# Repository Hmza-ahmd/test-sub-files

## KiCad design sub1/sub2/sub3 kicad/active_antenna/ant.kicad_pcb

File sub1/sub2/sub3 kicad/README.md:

[updated 28 May 2018]

Click image for full size.

[© bluebison.net](http://bluebison.net)

KiwiSDR
=======

Software-defined Radio (SDR) and GPS for the BeagleBone Black
----------------------------------------------------------------------

An add-on board ("cape") that turns your Beagle into a web-accessible shortwave receiver.

This repository contains the KiCAD files (schematics, board layout), Gerbers, BOM and other files used to produce the KiwiSDR PCB.
Also included here is the design for an active antenna and bias tee.

**Note: the active antenna and bias tee schematics and PCBs here are still undergoing development and do not work properly. Do not fabricate the PCBs and expect them to work.**

The KiwiSDR software is located in the repository [Beagle_SDR_GPS](https://github.com/jks-prv/Beagle_SDR_GPS/).

### Kickstarter
KiwiSDR had a successful [Kickstarter](https://www.kickstarter.com/projects/1575992013/kiwisdr-beaglebone-software-defined-radio-sdr-with/).

### Details

* Listen live: [SDR.hu](https://sdr.hu/?top=kiwi), [kiwisdr.com](http://kiwisdr.com/public), [rx.linkfanel.net](http://rx.linkfanel.net)
* [Project webpage](http://www.kiwisdr.com/)
* [Operating information: installation, operation, FAQ](http://www.kiwisdr.com/quickstart/)
* Latest [source code commits](https://github.com/jks-prv/Beagle_SDR_GPS/commits/master)
* [Design review document](https://www.dropbox.com/s/i1bjyp1acghnc16/KiwiSDR.design.review.pdf?dl=1)
* [Schematic](http://www.kiwisdr.com/docs/KiwiSDR/kiwi.schematic.pdf), [Gerbers](http://www.kiwisdr.com/docs/KiwiSDR/kiwi.gerbers.tar), [Active antenna](http://www.kiwisdr.com/docs/KiwiSDR/ant.pdf), [BOM ODS](http://www.kiwisdr.com/docs/KiwiSDR/kiwi.bom.ods), [BOM XLS](http://www.kiwisdr.com/docs/KiwiSDR/kiwi.bom.xls)

### Description
This SDR is a bit different. It has a web interface that can be used by up to four separate listeners. Each one listening and tuning an independent frequency simultaneously. See the screenshots below.

### Components
* SDR covering the 10 kHz to 30 MHz (VLF-HF) spectrum.
* Web interface based on [OpenWebRX](http://openwebrx.org/) from András Retzler, HA7ILM.
* Integrated software-defined GPS receiver from Andrew Holme's [Homemade GPS Receiver](http://www.aholme.co.uk/GPS/Main.htm).
* LTC 14-bit 65 MHz ADC.
* Xilinx Artix-7 A35 FPGA.
* Skyworks SE4150L GPS front-end.

### Features
* 100% Open Source / Open Hardware.
* Browser-based interface allowing multiple simultaneous user web connections (currently 4).
* Each connection tunes an independent receiver channel over the entire spectrum.
* Waterfall tunes independently of audio and includes zooming and panning.
* Multi-channel, parallel DDC design using bit-width optimized CIC filters.
* Good performance at VLF/LF since we personally spend time monitoring those frequencies.
* Automatic frequency calibration via received GPS timing.
* Easy hardware and software setup. Browser-based configuration interface.

### Status

Give the live receivers a try at the links above. You'll need a recent version of a modern web browser that supports HTML5. The web interface works, with some problems, on mobile devices. But there is no mobile version of the interface yet.

The files of a KiCAD PCB layout of the cape are available. This PCB has been fabricated in production quantities
and shipped to thousands of customers worldwide.
Please email us any comments you have after reviewing the design document above. The active antenna and injector PCBs have been fabricated and are undergoing development.

### Objectives

We wanted to design an SDR that provides certain features, at a low price point, that we felt weren't covered by current devices. The SDR must be web-accessible and simple to setup and use.
We also wanted to provide a self-contained platform for experimentation with SDR and GPS techniques. 

Most importantly, We'd really like to see a significant number of web-enabled, wide-band SDRs deployed in diverse locations world-wide because that makes possible some really interesting applications and experiments.

### Operation

Users can purchase just the KiwiSDR board or a complete "kit" consisting of the board, BeagleBone Green (software pre-installed), enclosure (assembly required), and GPS antenna (see [here](http://www.kiwisdr.com/)).
The software will try to automatically open up an incoming port through whatever Internet firewall/router may exist on the local network, but the user may have to perform this step manually. An antenna solution must be provided. An adequate power supply to the Beagle (e.g. 5V @ 2A) will also be required.

Four channels of audio and waterfall streamed over the Internet 24/7 requires about 30 GB per month. This is a common cap for many residential broadband plans. An automatic dynamic-DNS system is already part of the software so a web link to the SDR is immediately available with no configuration. Of course the system can be configured to only allow connections from the local network and ignore Internet connection requests.

### Web interface screenshots

Click images for full size.

View of entire 0-30 MHz range:

Moderate zoom of medium-wave broadcast band with spectrum display on top enabled:

Over-the-horizon-radar (OTHR) from Cyprus showing short-term ionospheric fluctuations:

VLF/LF reception in New Zealand

| kHz | Station | Location | Signal |
| :-- | :------ | :------- | :----- |
| 12.88 | Alpha | Khabarovsk & Novosibirsk Russia | Navigation system |
| 17.0 | VTX2 | India | MSK comms |
| 19.8 | NWC | Australia | MSK comms |
| 21.4 | NPM | Hawaii | MSK comms |
| 22.2 | NDT/JJI | Japan | MSK comms |
| 24.1 | (UNID) | Korea, per David L Wilson | FSK comms |
| 40.0 | JJY | Japan | Time signal |
| 45.9 | NSY | Italy | MSK comms |
| 54.0 | NDI | Japan | MSK comms |
| 60.0 | JJY/WWVB | Japan, USA | Time signals |
| 68.5 | BPC | China | Time signal |

Many others heard during different times and conditions.

[end-of-document]

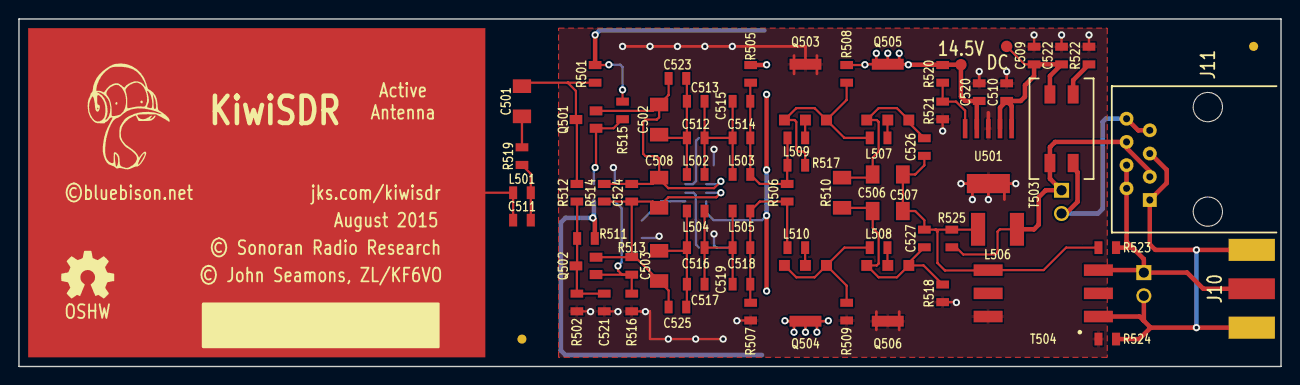
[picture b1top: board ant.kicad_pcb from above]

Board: 2 copper layers, 138.0 x 38.0 mm, 85 parts (0 on the bottom side), 36 nets.

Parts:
C501, C502, C503, C506, C507, C508: 470n/100; kiwi-SM1206
C504, C505: DNL 470n/100; kiwi-SM1206
C509: 100n/100; kiwi-SM0805
C510, C520: 10u/25; kiwi-SM0805
C511, C512, C513, C514, C515, C516, C517, C518, C519: DNL; kiwi-SM0805
C521: DNL 100n/100; kiwi-SM0805
C522, C523, C524, C525, C526, C527: 1n/100; kiwi-SM0805
EP501: E_FIELD_PROBE; kiwi-E_FIELD_PROBE
FID1, FID2: FIDUCIAL; kiwi-FIDUCIAL_2_SIDE
GFX1: LOGO; kiwi-KIWI_10MM
GFX3: OSHW; kiwi-OSHW_6MM
J10: DNL BNC; kiwi-BNC_SMA_NO_VIP
J11: DNL RJ45; kiwi-RJ45_8
J12: DNL TB_2; kiwi-TB_2P_2_54MM
J13: TB_2; kiwi-TB_2P_2_54MM
L501, L502, L503, L504, L505: 0R; kiwi-SM0805
L506: 100uH; kiwi-SM1812
L507, L508, L509, L510: FB 80Z; kiwi-SM0805
Q501: J310; kiwi-SOT23_DGS
Q502: J271; kiwi-SOT23_DGS
Q503, Q506: BFG31; kiwi-SOT223_EBEC
Q504, Q505: BFG35; kiwi-SOT223_EBEC
Q507: DNL J310; kiwi-SOT23_DGS
R501, R502: 1M; kiwi-SM0805
R503, R504: DNL 100R; kiwi-SM0805
R505, R507: 100K; kiwi-SM0805
R506: 2K2; kiwi-SM0805
R508, R509: 470R; kiwi-SM0805
R510: 10R/0.66W; kiwi-SM1206
R511: DNL 1M; kiwi-SM0805
R512, R515, R516, R519, R523, R524: 0R; kiwi-SM0805
R513, R518: DNL 0R; kiwi-SM0805
R514: 100R; kiwi-SM0805
R517: DNL 47R; kiwi-SM0805
R520: 11K; kiwi-SM0805
R521: 1K; kiwi-SM0805
R522: DNL; kiwi-SM0805
R525: 1K5; kiwi-SM0805
T501: DNL T-622; kiwi-MCL_KK81
T502, T504: DNL T1-6; kiwi-MCL_KK81
T503: CMC 2 mH; kiwi-CMC
TP501, TP502: TEST_POINT; kiwi-TP_1250
U501: TPS7A4501; kiwi-SOT223_6

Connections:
/14.55: C520.1, Q504.C, Q505.C, R501.1, R503.1, R505.1, R508.1, R511.1, R515.1, R520.1, T501.3, T502.4, TP502.1, U501.4
/ANT2: C511.2, L501.1, R519.1
/ANT3: C501.1, R519.2
/ANT4: C501.2, Q501.G, R501.2, R512.1
/B1H: L509.2, Q503.B
/B1L: L510.2, Q504.B
/B2H: L507.2, Q505.B
/B2L: L508.2, Q506.B
/BIAS: C521.1, Q502.G, R502.2, R511.2, R512.2
/BIAS+: J11.3, J11.6, J12.1, L506.2, R525.1, T503.3
/BIAS-: J11.7, J11.8, J12.2, T503.4
/DCIN: C509.1, C510.1, C522.1, T503.2, TP501.1, U501.1, U501.2
/E1H: L507.1, Q503.E1, Q503.E2, R508.2, R517.1
/E1L: L508.1, Q504.E1, Q504.E2, R509.1
/E2H: C506.1, C526.1, Q505.E1, Q505.E2, R510.1
/E2L: C507.1, C527.1, Q506.E1, Q506.E2, R510.2, R518.1
/EPROBE: C511.1, EP501.1, L501.2
/FB1: Q501.D, R515.2, T502.6
/FB2: Q502.D, Q507.G, R513.1, R516.2, T502.3
/FB3: Q507.D, T501.4
/JHI: C502.1, C508.1, C523.1, C524.1, Q501.S, R514.2, T501.1
/JLO: C503.1, C508.2, C524.2, C525.1, Q502.S, R513.2, R514.1, T501.2
/NF1H: C502.2, C512.1, C513.1, C523.2, L502.1
/NF1L: C503.2, C516.1, C517.1, C525.2, L504.1
/NF2H: C512.2, C513.2, C514.1, C515.1, L502.2, L503.1
/NF2L: C516.2, C517.2, C518.1, C519.1, L504.2, L505.1
/NF3H: C514.2, C515.2, L503.2, L509.1, R505.2, R506.1, R517.2
/NF3L: C518.2, C519.2, L505.2, L510.1, R506.2, R507.1
/OUT: C506.2, C507.2, C526.2, C527.2, L506.1, R523.2, R525.2, T504.3
/RX+: J10.1, J11.2, J11.4, J13.1, R523.1, T504.4
/RX-: J10.2, J10.3, J11.1, J11.5, J13.2, R524.1, T504.6
/THI: C505.1, R504.2, T501.6
/TLO: C504.2, R503.2, T501.5
/TP: R522.1, T503.1
/VADJ: R520.2, R521.2, U501.5
GND: C504.1, C505.2, C509.2, C510.2, C520.2, C521.2, C522.2, Q503.C, Q506.C, Q507.S, R502.1, R504.1, R507.2, R509.2, R516.1, R518.2, R521.1, R522.2, R524.2, T502.1, T504.1, U501.3, U501.TAB

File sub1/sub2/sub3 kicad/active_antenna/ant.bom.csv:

#1, 11, 0R, Panasonic, ERJ-6GEY0R00V, kiwi-SM0805, L501 L502 L503 L504 L505 R512 R515 R516 R519 R523 R524
#2, 1, 100R, Panasonic, ERJ-6ENF1000V, kiwi-SM0805, R514
#3, 2, 470R, Panasonic, ERJ-6ENF4700V, kiwi-SM0805, R508 R509
#4, 1, 1K, Panasonic, ERJ-6ENF1001V, kiwi-SM0805, R521
#5, 1, 1K5, Panasonic, ERJ-6ENF1501V, kiwi-SM0805, R525
#6, 1, 2K2, Panasonic, ERJ-6ENF2201V, kiwi-SM0805, R506
#7, 1, 11K, Panasonic, ERJ-6ENF1102V, kiwi-SM0805, R520
#8, 2, 100K, Panasonic, ERJ-6ENF1003V, kiwi-SM0805, R505 R507
#9, 2, 1M, Panasonic, ERJ-6ENF1004V, kiwi-SM0805, R501 R502
#10, 1, 10R/0.66W, Panasonic, ERJ-P08F10R0V, kiwi-SM1206, R510
#11, 6, 1n/100, Murata, GRM219R72A102KA01J, kiwi-SM0805, C522 C523 C524 C525 C526 C527
#12, 1, 100n/100, Murata, GRM21BR72A103KA01L, kiwi-SM0805, C509
#13, 2, 10u/25, Murata, GRM219R61E106KA12D, kiwi-SM0805, C510 C520
#14, 6, 470n/100, AVX, ESD61C474K4T2A-28, kiwi-SM1206, C501 C502 C503 C506 C507 C508
#15, 1, 100uH, TDK, B82432T1104K, kiwi-SM1812, L506
#16, 1, CMC 2 mH, Bourns, SRF0905A-202Y, kiwi-CMC, T503
#17, 1, J310, Fairchild, MMBFJ310, kiwi-SOT23_DGS, Q501
#18, 1, J271, Fairchild, MMBFJ271, kiwi-SOT23_DGS, Q502
#19, 2, BFG31, NXP, BFG31.115, kiwi-SOT223_EBEC, Q503 Q506
#20, 2, BFG35, NXP, BFG35.115, kiwi-SOT223_EBEC, Q504 Q505
#21, 1, TPS7A4501, TI, TPS7A4501DCQR, kiwi-SOT223_6, U501
#22, 4, FB 80Z, TDK, MMZ2012D800B, kiwi-SM0805, L507 L508 L509 L510
#23, 2, TB_2, TE Conn, 282834-2, kiwi-TB_2P_2_54MM, J12 J13
#24, 1, SMA, Molex, 73251-1150, kiwi-BNC_SMA_NO_VIP, J10
#25, 1, RJ45, FCI, 54602-908LF, kiwi-RJ45_8, J11

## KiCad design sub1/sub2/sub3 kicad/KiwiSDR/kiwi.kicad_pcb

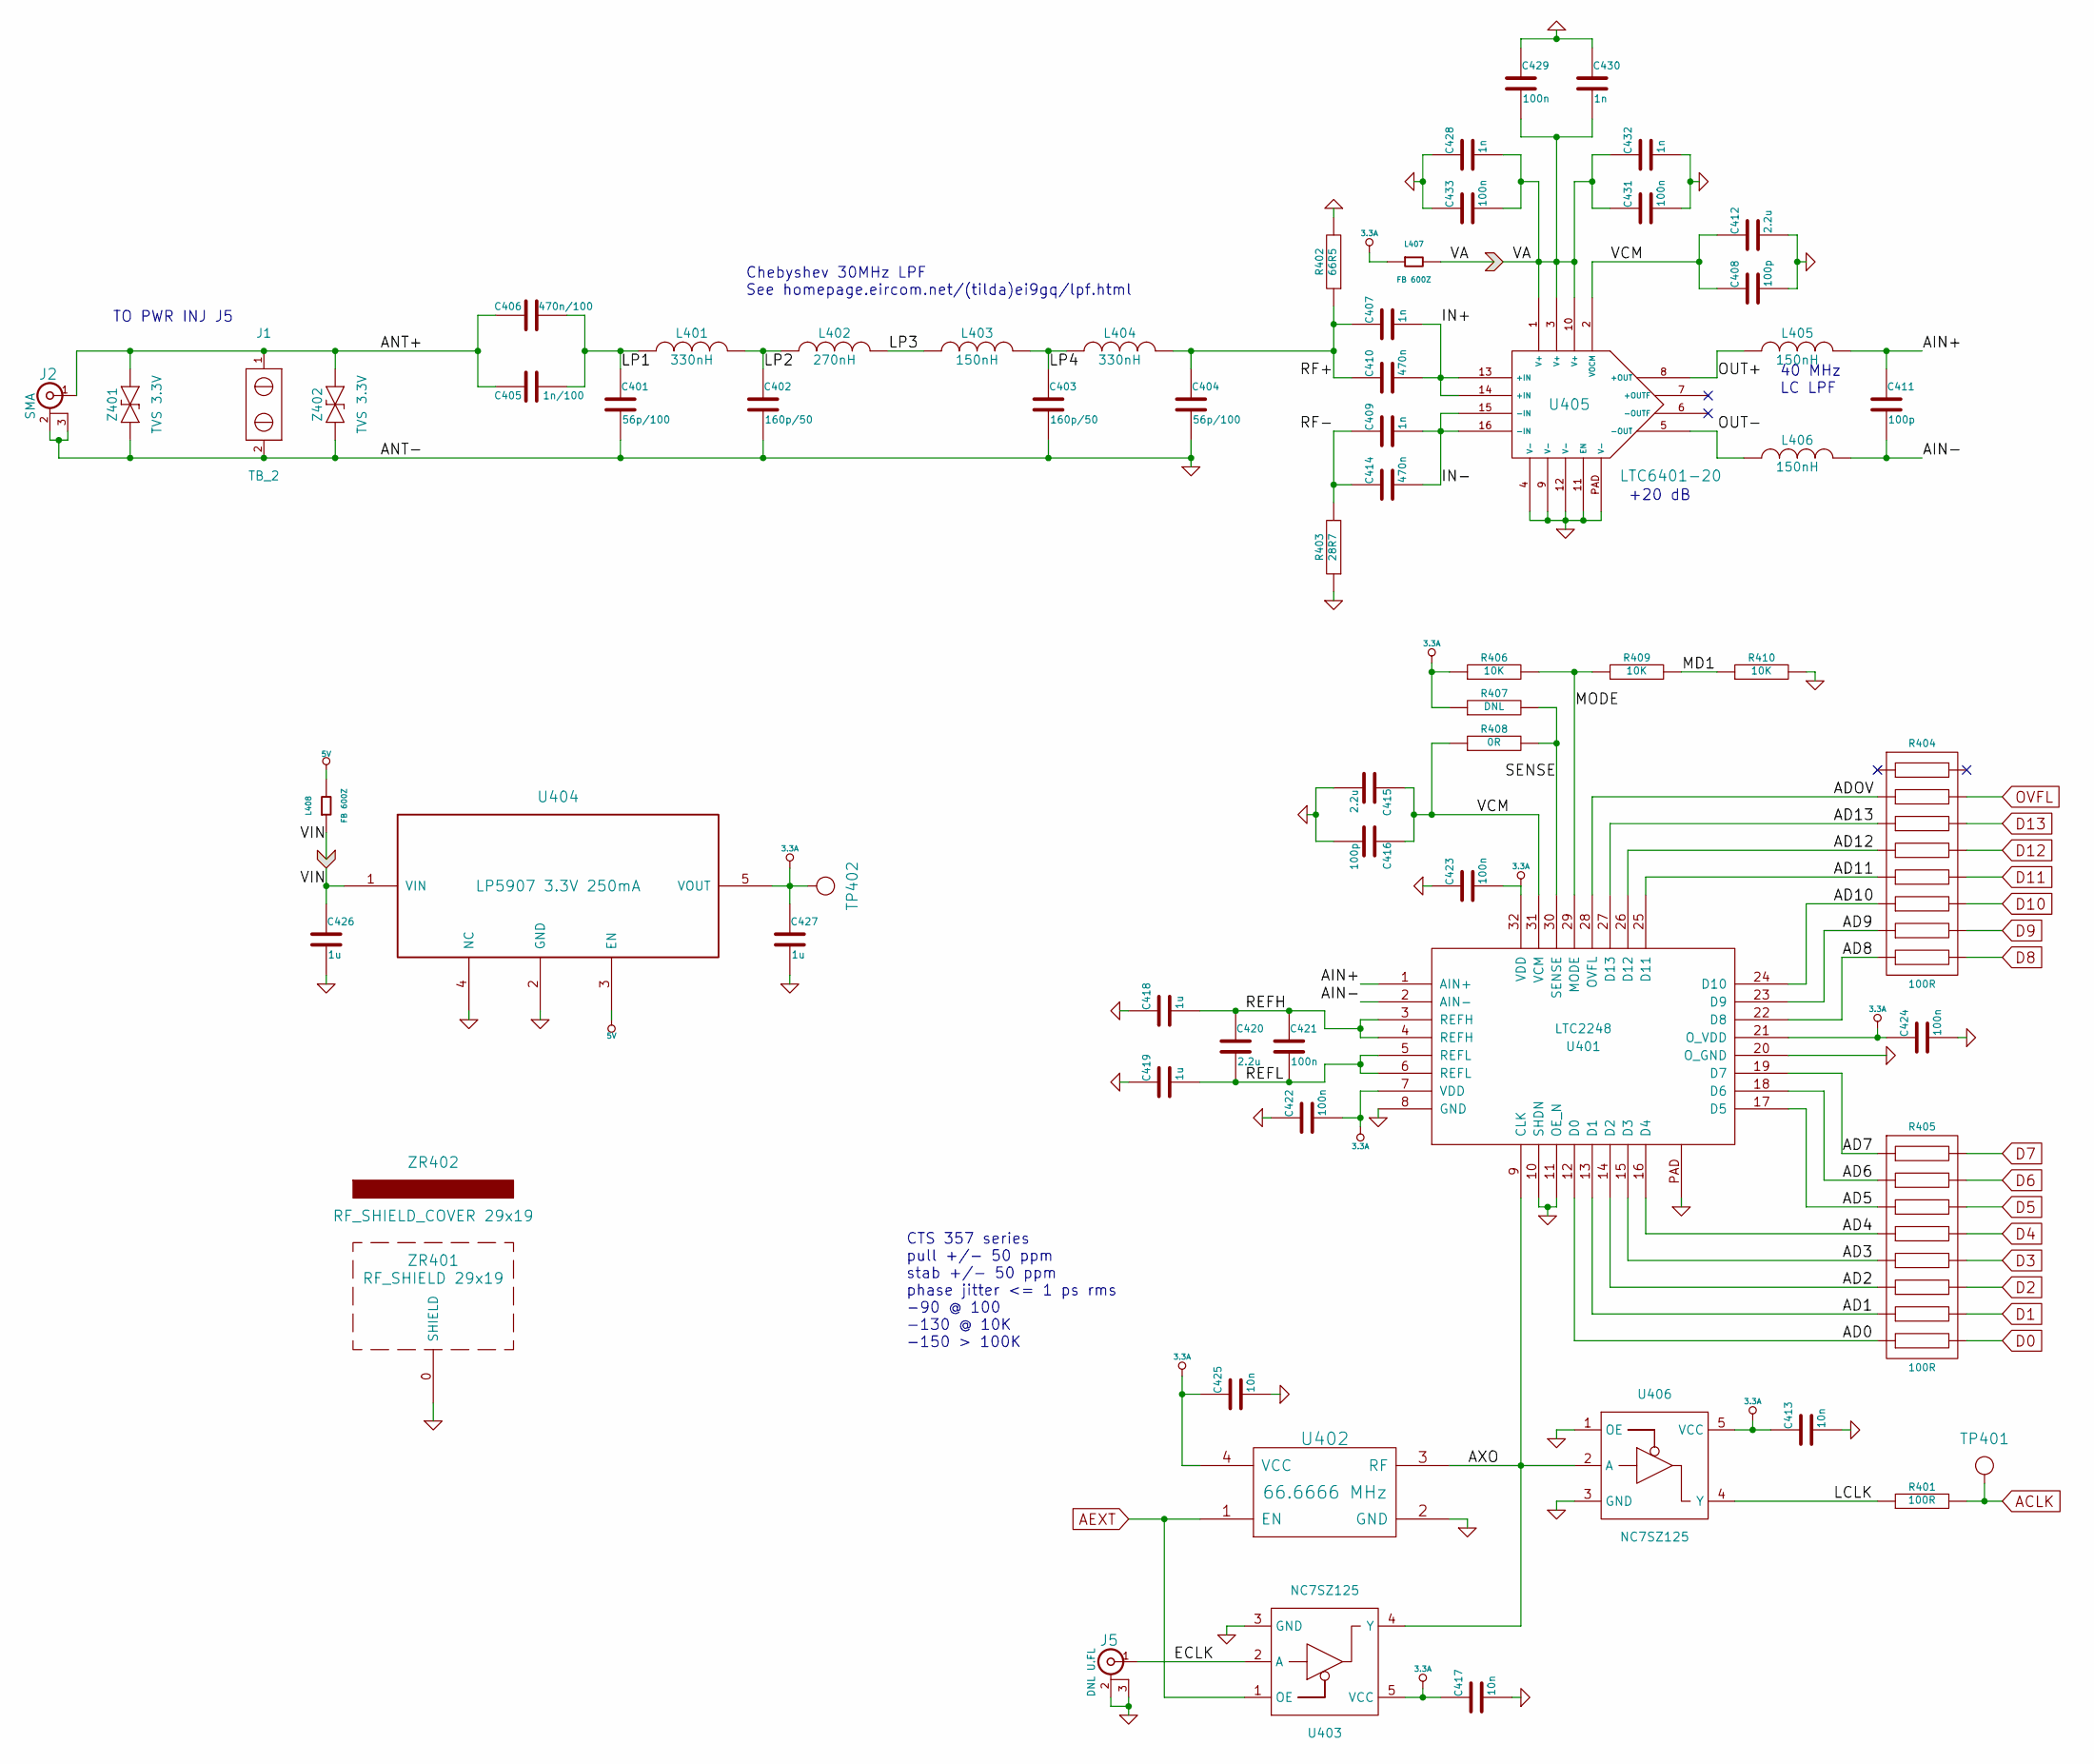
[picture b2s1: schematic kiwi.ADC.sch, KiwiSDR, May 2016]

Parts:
C401, C404: 56p/100; kiwi-SM0402
C402, C403: 160p/50; kiwi-SM0402
C405: 1n/100; kiwi-SM0805
C406: 470n/100; kiwi-SM1206
C407, C409, C428, C430, C432: 1n; kiwi-SM0402
C408, C411, C416: 100p; kiwi-SM0402
C410, C414: 470n; kiwi-SM0402
C412, C415, C420: 2.2u; kiwi-SM0402
C413, C417, C425: 10n; kiwi-SM0402
C418, C419, C426, C427: 1u; kiwi-SM0402
C421, C422, C423, C424, C429, C431, C433: 100n; kiwi-SM0402
J1: TB_2; kiwi-TB_2P_2_54MM
J2: SMA; kiwi-SMA_OPL_EM
J5: DNL U.FL; kiwi-U.FL
L401, L404: 330nH; kiwi-SM0402
L402: 270nH; kiwi-SM0402
L403, L405, L406: 150nH; kiwi-SM0402
L407, L408: FB 600Z; kiwi-SM0402
R401: 100R; kiwi-SM0402
R402: 66R5; kiwi-SM0402
R403: 28R7; kiwi-SM0402
R404, R405: 100R; kiwi-RNET_CAY16_J8
R406, R409, R410: 10K; kiwi-SM0402
R407: DNL; kiwi-SM0402
R408: 0R; kiwi-SM0402
TP401: TEST_POINT; kiwi-TP_600
TP402: TEST_POINT; kiwi-TP_VIA_600
U401: LTC2248; kiwi-QFN32
U402: 66.6666 MHz; kiwi-XO
U403, U406: NC7SZ125; kiwi-SC70_5
U404: LP5907 3.3V 250mA; kiwi-SOT23_5
U405: LTC6401-20; kiwi-QFN16
Z401, Z402: TVS 3.3V; kiwi-SOD323
ZR401: RF_SHIELD 29x19; kiwi-RF_SHIELD_29x19
ZR402: RF_SHIELD_COVER 29x19; kiwi-RF_SHIELD_COVER

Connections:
3.3A: C413.1, C417.1, C422.2, C423.2, C424.1, C425.1, C427.1, L407.1, R406.1, R407.1, TP402.1, U401.7 (VDD), U401.21 (O_VDD), U401.32 (VDD), U402.4 (VCC), U403.5 (VCC), U404.5 (VOUT), U406.5 (VCC)
/ADC/AD0: R405.15, U401.12 (D0)
/ADC/AD1: R405.13, U401.13 (D1)
/ADC/AD2: R405.11, U401.14 (D2)
/ADC/AD3: R405.9, U401.15 (D3)
/ADC/AD4: R405.7, U401.16 (D4)
/ADC/AD5: R405.5, U401.17 (D5)
/ADC/AD6: R405.3, U401.18 (D6)
/ADC/AD7: R405.1, U401.19 (D7)
/ADC/AD8: R404.15, U401.22 (D8)
/ADC/AD9: R404.13, U401.23 (D9)
/ADC/AD10: R404.11, U401.24 (D10)
/ADC/AD11: R404.9, U401.25 (D11)
/ADC/AD12: R404.7, U401.26 (D12)
/ADC/AD13: R404.5, U401.27 (D13)
/ADC/ADOV: R404.3, U401.28 (OVFL)
/ADC/AIN+: C411.1, L405.2, U401.1 (AIN+)
/ADC/AIN-: C411.2, L406.2, U401.2 (AIN-)
/ADC/ANT+: C405.1, C406.1, J1.1, J2.1 (In), Z401.2, Z402.2
/ADC/AXO: U401.9 (CLK), U402.3 (RF), U403.4 (Y), U406.2 (A)
/ADC/ECLK: J5.1 (In), U403.2 (A)
/ADC/IN+: C407.2, C410.2, U405.13 (+IN), U405.14 (+IN)
/ADC/IN-: C409.2, C414.2, U405.15 (-IN), U405.16 (-IN)
/ADC/LCLK: R401.1, U406.4 (Y)
/ADC/LP1: C401.1, C405.2, C406.2, L401.1
/ADC/LP2: C402.1, L401.2, L402.1
/ADC/LP3: L402.2, L403.1
/ADC/LP4: C403.1, L403.2, L404.1
/ADC/MD1: R409.2, R410.1
/ADC/MODE: R406.2, R409.1, U401.29 (MODE)
/ADC/OUT+: L405.1, U405.8 (+OUT)
/ADC/OUT-: L406.1, U405.5 (-OUT)
/ADC/REFH: C418.2, C420.1, C421.1, U401.3 (REFH), U401.4 (REFH)
/ADC/REFL: C419.2, C420.2, C421.2, U401.5 (REFL), U401.6 (REFL)
/ADC/RF+: C404.1, C407.1, C410.1, L404.2, R402.1
/ADC/RF-: C409.1, C414.1, R403.2
/ADC/SENSE: R407.2, R408.2, U401.30 (SENSE)
/ADC/VCM: C408.1, C412.1, C415.1, C416.1, R408.1, U401.31 (VCM), U405.2 (VOCM)
ACLK: R401.2, TP401.1; also elsewhere on the board
AEXT: U402.1 (EN), U403.1 (OE); also elsewhere on the board
D0: R405.16; also elsewhere on the board
D1: R405.14; also elsewhere on the board
D2: R405.12; also elsewhere on the board
D3: R405.10; also elsewhere on the board
D4: R405.8; also elsewhere on the board
D5: R405.6; also elsewhere on the board
D6: R405.4; also elsewhere on the board
D7: R405.2; also elsewhere on the board
D8: R404.16; also elsewhere on the board
D9: R404.14; also elsewhere on the board
D10: R404.12; also elsewhere on the board
D11: R404.10; also elsewhere on the board
D12: R404.8; also elsewhere on the board
D13: R404.6; also elsewhere on the board
OVFL: R404.4; also elsewhere on the board

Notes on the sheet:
CTS 357 series pull +/- 50 ppm stab +/- 50 ppm phase jitter <= 1 ps rms -90 @ 100 -130 @ 10K -150 > 100K
Chebyshev 30MHz LPF See homepage.eircom.net/(tilda)ei9gq/lpf.html
40 MHz LC LPF
+20 dB
TO PWR INJ J5

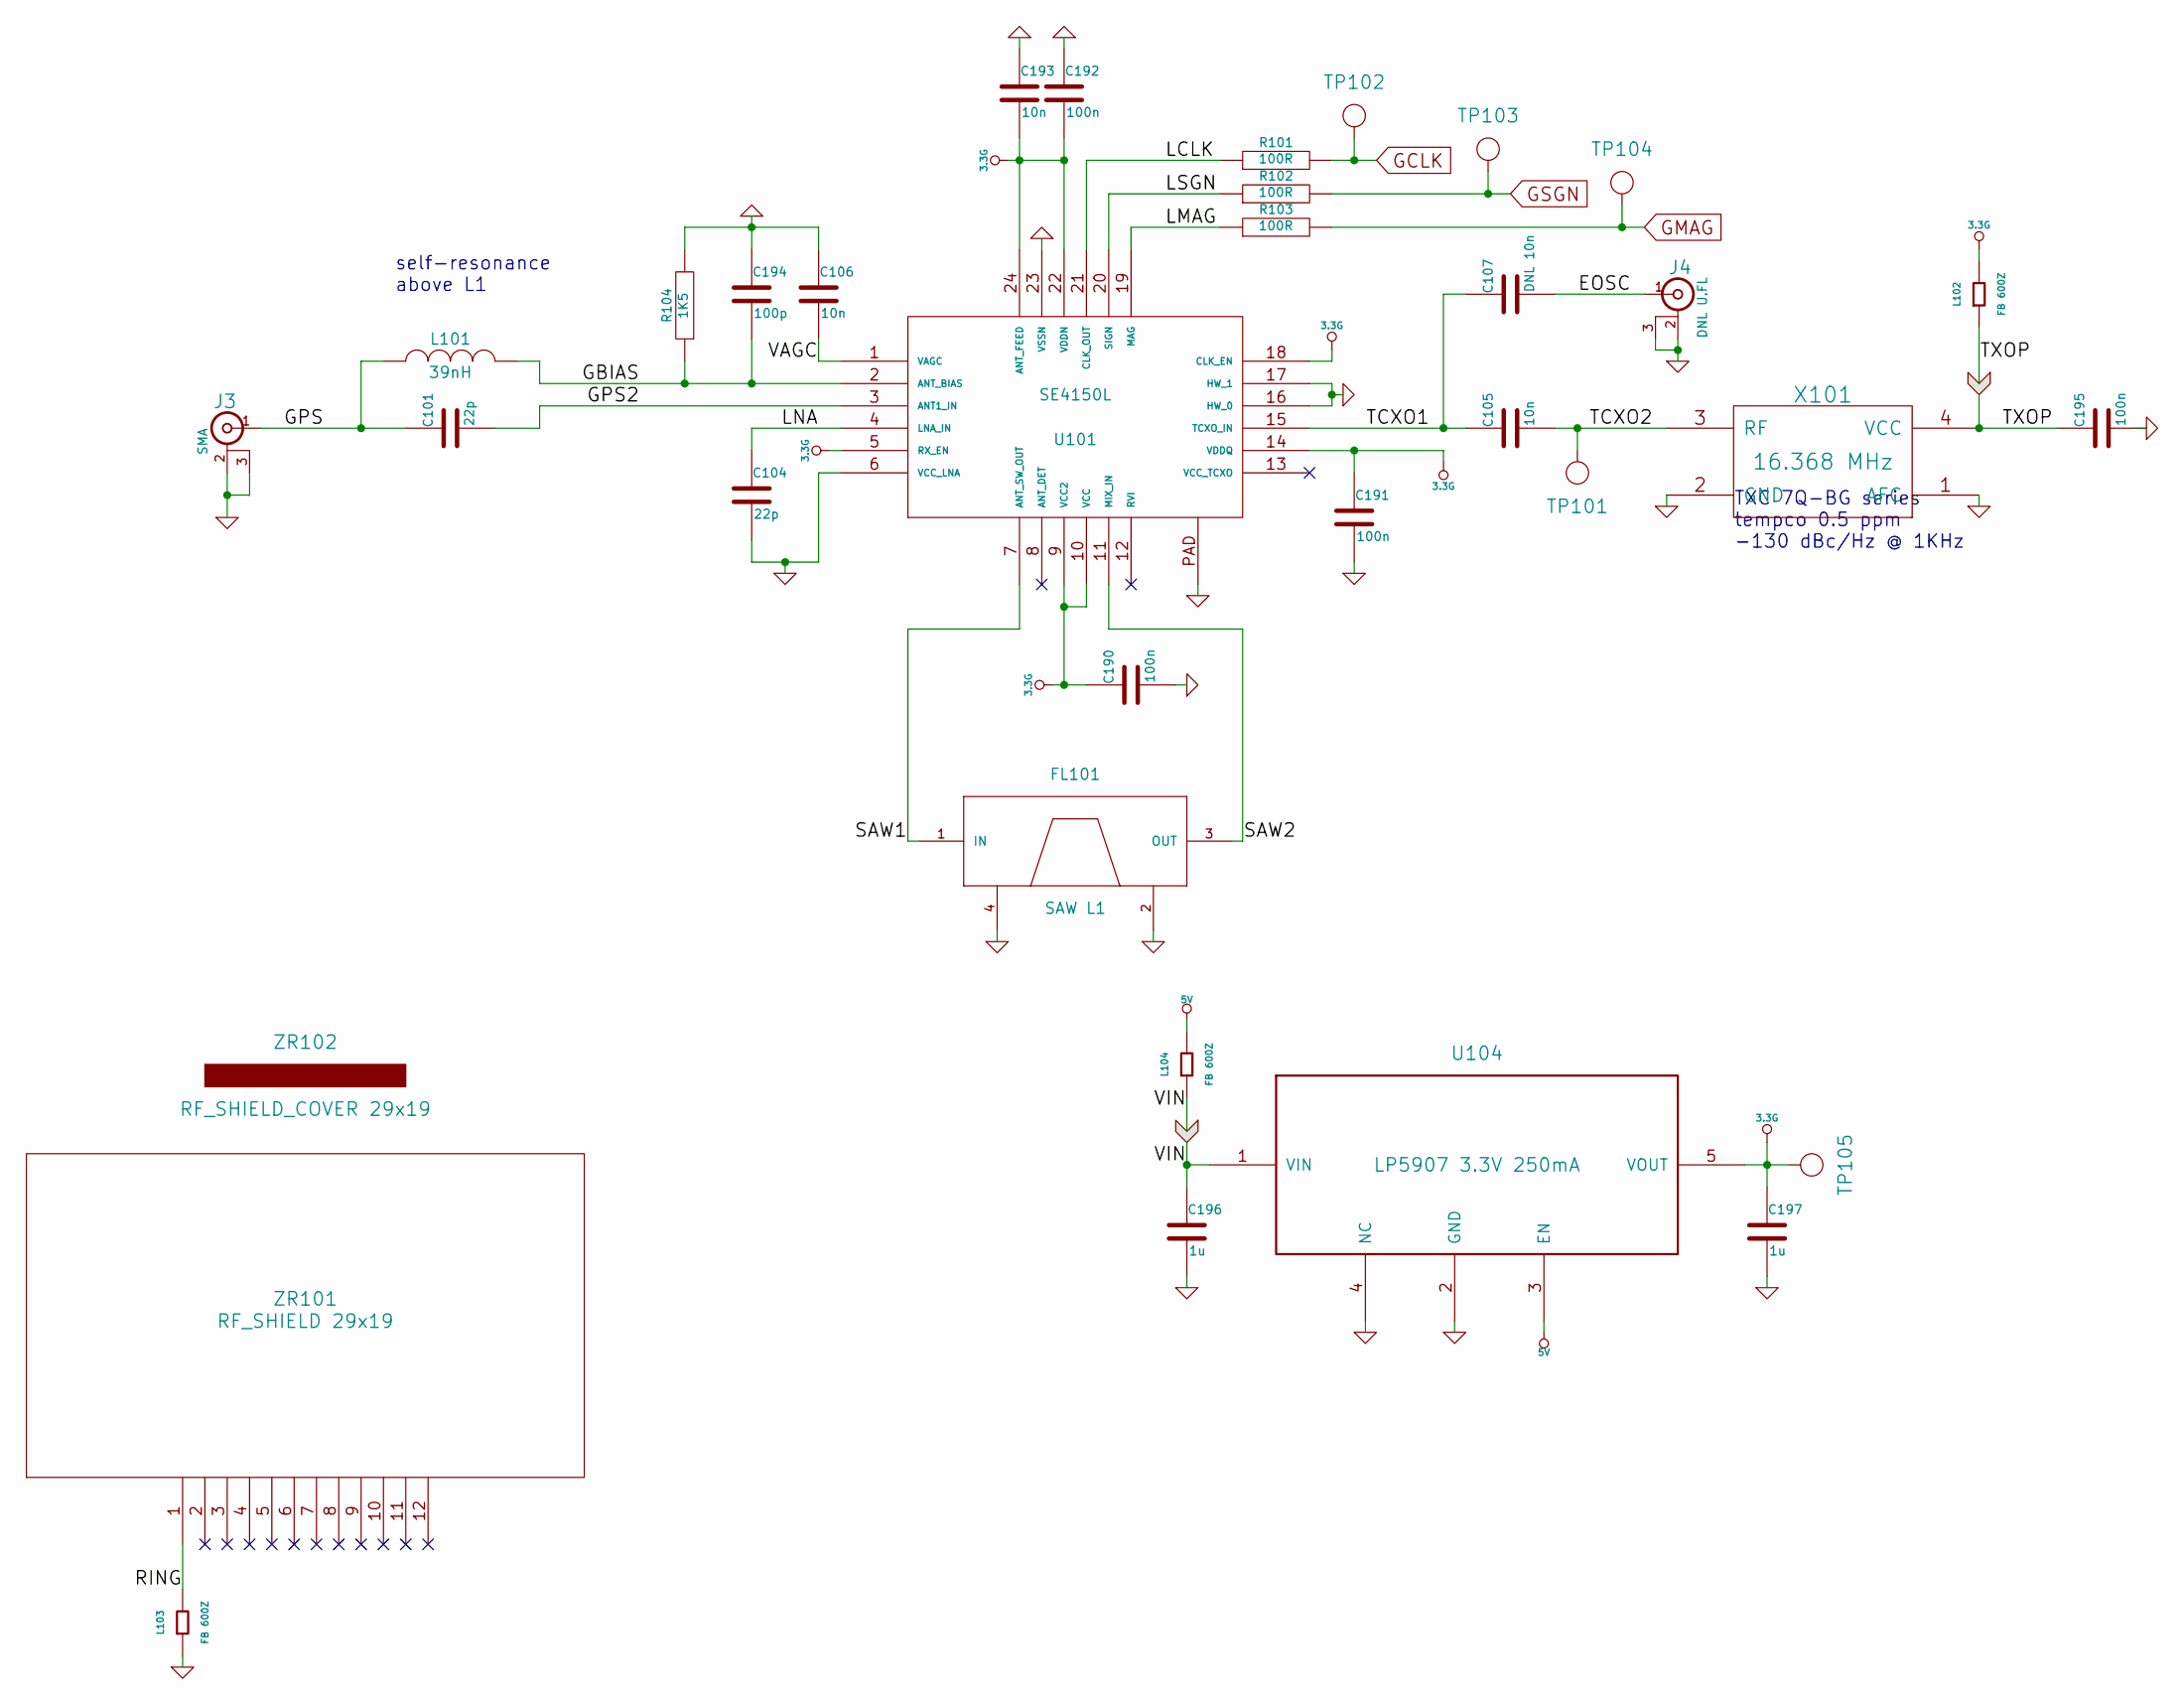
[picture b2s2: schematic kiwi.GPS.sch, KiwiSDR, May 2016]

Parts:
C101, C104: 22p; kiwi-SM0402
C105, C106, C193: 10n; kiwi-SM0402
C107: DNL 10n; kiwi-SM0402
C190, C191, C192, C195: 100n; kiwi-SM0402
C194: 100p; kiwi-SM0402
C196, C197: 1u; kiwi-SM0402
FL101: SAW L1; kiwi-SAW
J3: SMA; kiwi-SMA_OPL_EM
J4: DNL U.FL; kiwi-U.FL
L101: 39nH; kiwi-SM0402
L102, L103, L104: FB 600Z; kiwi-SM0402
R101, R102, R103: 100R; kiwi-SM0402
R104: 1K5; kiwi-SM0402
TP101, TP105: TEST_POINT; kiwi-TP_600
TP102, TP103, TP104: TEST_POINT; kiwi-TP_VIA_1250
U101: SE4150L; kiwi-QFN24
U104: LP5907 3.3V 250mA; kiwi-SOT23_5
X101: 16.368 MHz; kiwi-TCXO
ZR101: RF_SHIELD 29x19; kiwi-RF_SHIELD_29x19_16P
ZR102: RF_SHIELD_COVER 29x19; kiwi-RF_SHIELD_COVER

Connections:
3.3G: C190.1, C191.1, C192.2, C193.2, C197.1, L102.2, TP105.1, U101.5 (RX_EN), U101.9 (VCC2), U101.10 (VCC), U101.14 (VDDQ), U101.18 (CLK_EN), U101.22 (VDDN), U101.24 (ANT_FEED), U104.5 (VOUT)
/GPS/EOSC: C107.2, J4.1 (In)
/GPS/GBIAS: C194.2, L101.2, R104.1, U101.2 (ANT_BIAS)
/GPS/GPS: C101.1, J3.1 (In), L101.1
/GPS/GPS2: C101.2, U101.3 (ANT1_IN)
/GPS/LCLK: R101.1, U101.21 (CLK_OUT)
/GPS/LMAG: R103.1, U101.19 (MAG)
/GPS/LNA: C104.1, U101.4 (LNA_IN)
/GPS/LSGN: R102.1, U101.20 (SIGN)
/GPS/RING: L103.2, ZR101.1
/GPS/SAW1: FL101.1 (IN), U101.7 (ANT_SW_OUT)
/GPS/SAW2: FL101.3 (OUT), U101.11 (MIX_IN)
/GPS/TCXO1: C105.1, C107.1, U101.15 (TCXO_IN)
/GPS/TCXO2: C105.2, TP101.1, X101.3 (RF)
/GPS/VAGC: C106.2, U101.1 (VAGC)
GCLK: R101.2, TP102.1; also elsewhere on the board
GMAG: R103.2, TP104.1; also elsewhere on the board
GSGN: R102.2, TP103.1; also elsewhere on the board

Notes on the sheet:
self-resonance above L1
TXC 7Q-BG series tempco 0.5 ppm -130 dBc/Hz @ 1KHz

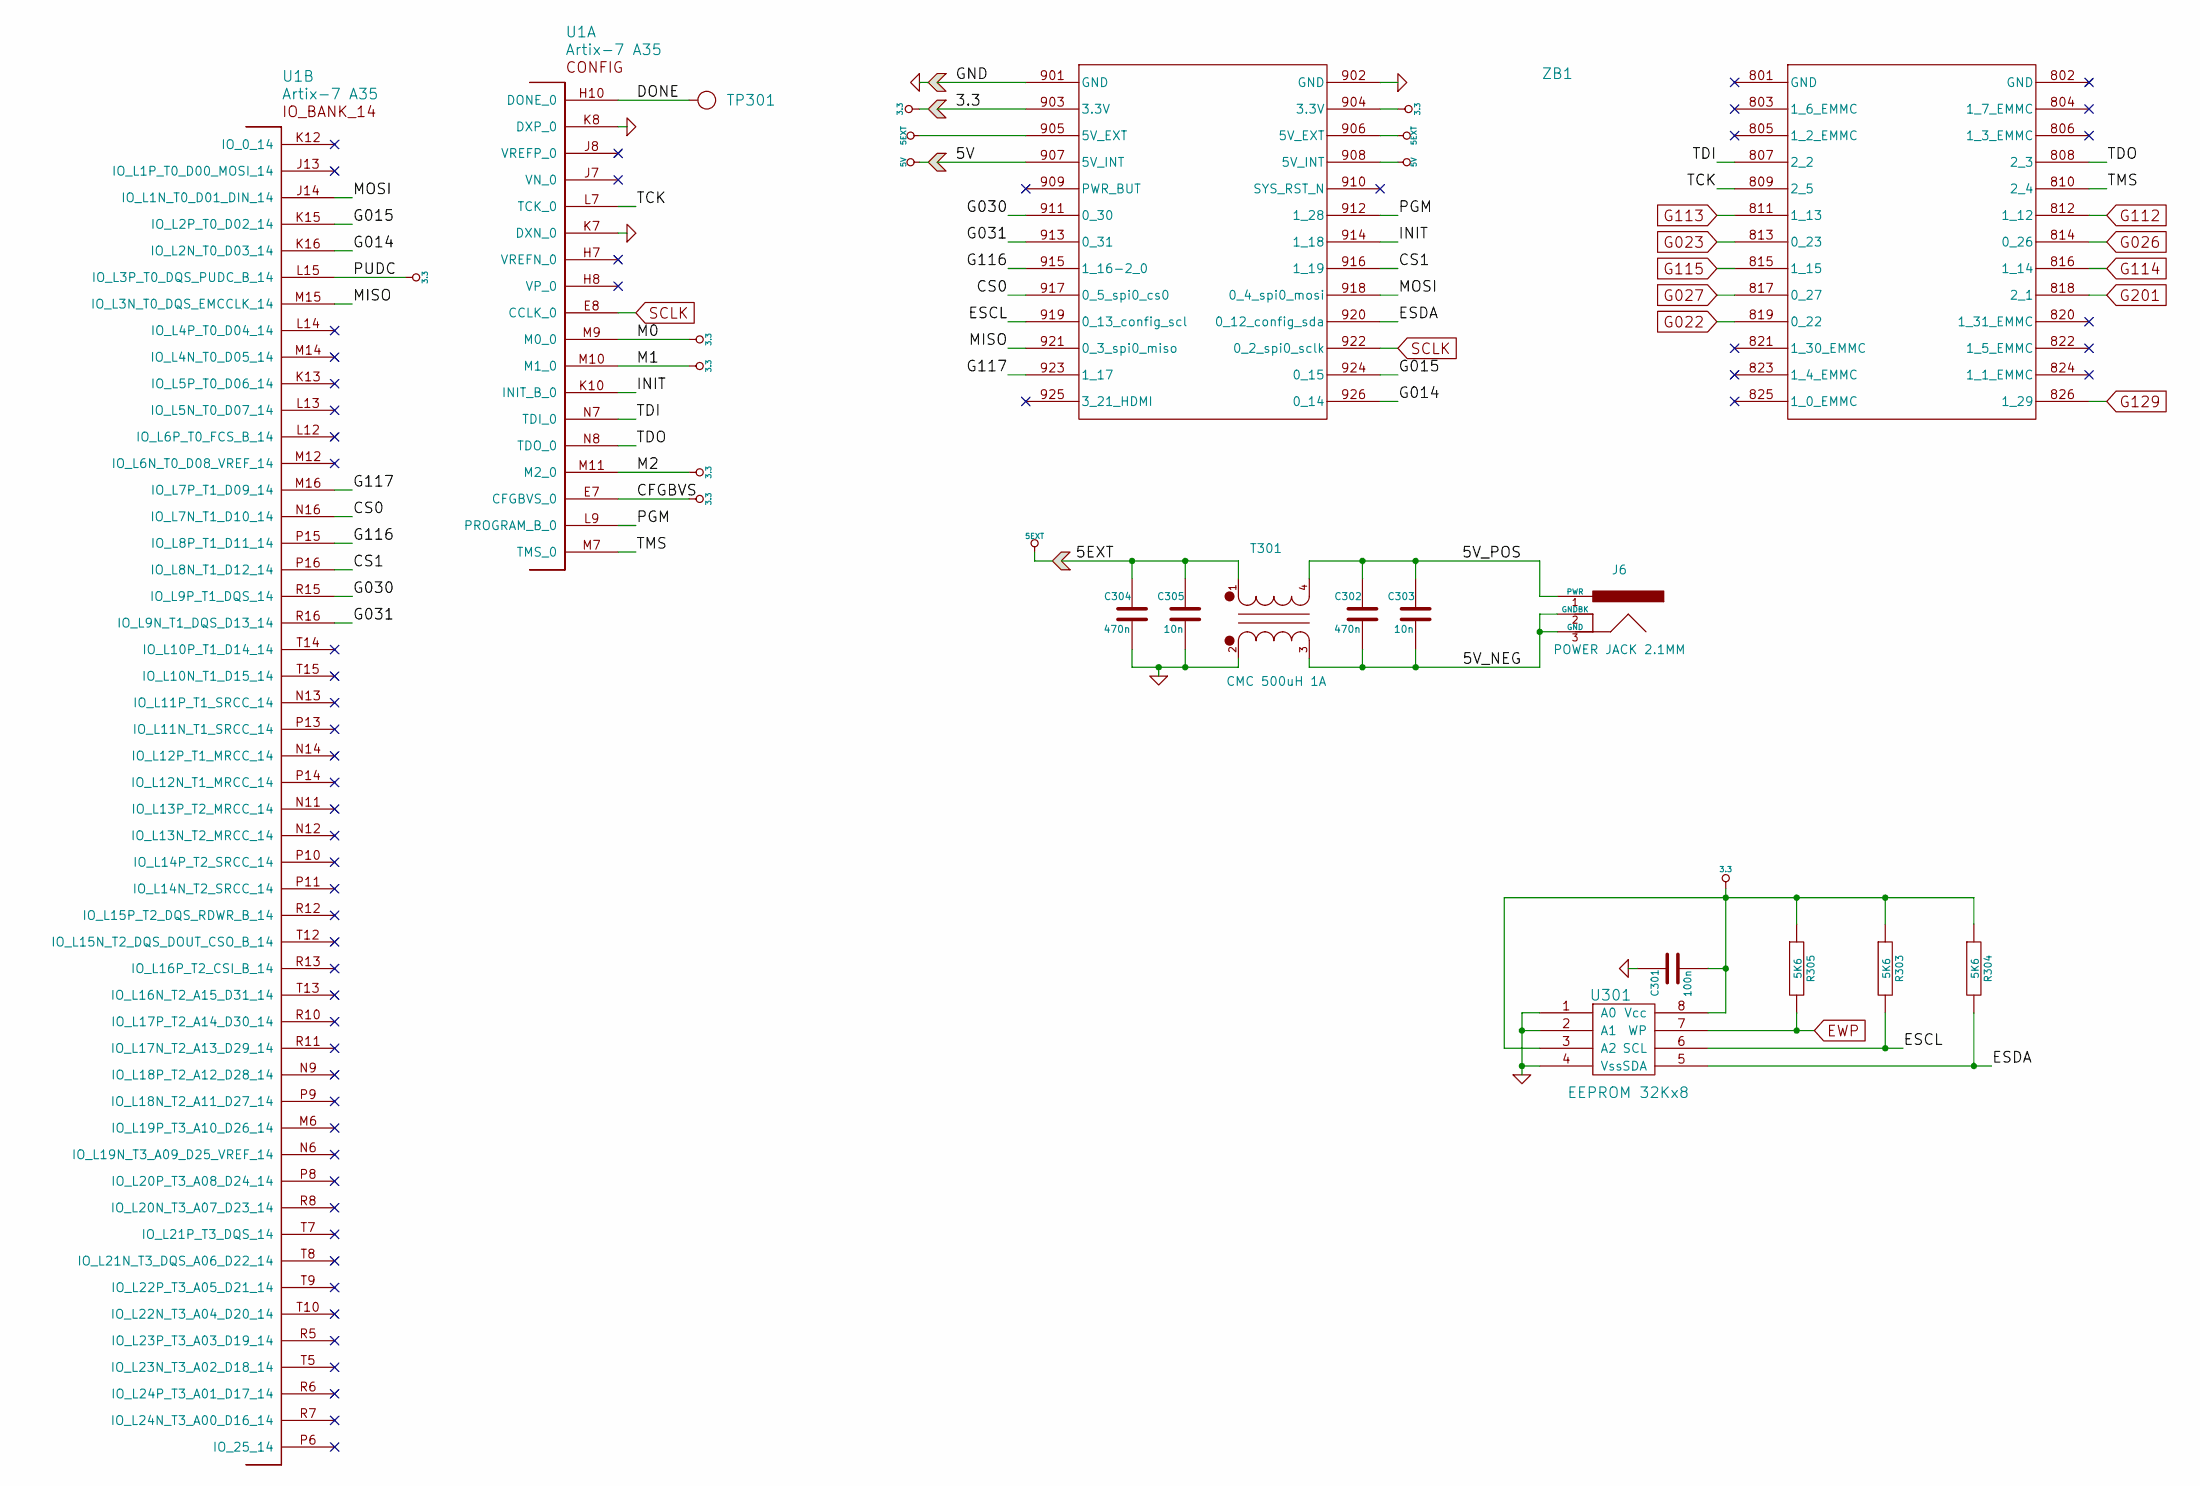
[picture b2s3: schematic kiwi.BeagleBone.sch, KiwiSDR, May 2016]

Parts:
C301: 100n; kiwi-SM0402
C302, C304: 470n; kiwi-SM0402
C303, C305: 10n; kiwi-SM0402
J6: POWER JACK 2.1MM; kiwi-JACK_2_1MM_TH
R303, R304, R305: 5K6; kiwi-SM0402
T301: CMC 500uH 1A; kiwi-CMC
TP301: TEST_POINT; kiwi-TP_VIA_600
U1: Artix-7 A35; kiwi-FTG256
U301: EEPROM 32Kx8; kiwi-TSSOP8
ZB1: HEADER 13x2; kiwi-BEAGLEBONE_BLACK

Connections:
/BeagleBone/5V_NEG: C302.2, C303.2, J6.2 (GNDBK), J6.3 (GND), T301.3
/BeagleBone/5V_POS: C302.1, C303.1, J6.1 (PWR), T301.4
/BeagleBone/CS0: U1.N16 (IO_L7N_T1_D10_14), ZB1.917 (0_5_spi0_cs0)
/BeagleBone/CS1: U1.P16 (IO_L8N_T1_D12_14), ZB1.916 (1_19)
/BeagleBone/DONE: TP301.1, U1.H10 (DONE_0)
/BeagleBone/ESCL: R303.2, U301.6 (SCL), ZB1.919 (0_13_config_scl)
/BeagleBone/ESDA: R304.2, U301.5 (SDA), ZB1.920 (0_12_config_sda)
/BeagleBone/G014: U1.K16 (IO_L2N_T0_D03_14), ZB1.926 (0_14)
/BeagleBone/G015: U1.K15 (IO_L2P_T0_D02_14), ZB1.924 (0_15)
/BeagleBone/G030: U1.R15 (IO_L9P_T1_DQS_14), ZB1.911 (0_30)
/BeagleBone/G031: U1.R16 (IO_L9N_T1_DQS_D13_14), ZB1.913 (0_31)
/BeagleBone/G116: U1.P15 (IO_L8P_T1_D11_14), ZB1.915 (1_16-2_0)
/BeagleBone/G117: U1.M16 (IO_L7P_T1_D09_14), ZB1.923 (1_17)
/BeagleBone/INIT: U1.K10 (INIT_B_0), ZB1.914 (1_18)
/BeagleBone/MISO: U1.M15 (IO_L3N_T0_DQS_EMCCLK_14), ZB1.921 (0_3_spi0_miso)
/BeagleBone/MOSI: U1.J14 (IO_L1N_T0_D01_DIN_14), ZB1.918 (0_4_spi0_mosi)
/BeagleBone/PGM: U1.L9 (PROGRAM_B_0), ZB1.912 (1_28)
/BeagleBone/TCK: U1.L7 (TCK_0), ZB1.809 (2_5)
/BeagleBone/TDI: U1.N7 (TDI_0), ZB1.807 (2_2)
/BeagleBone/TDO: U1.N8 (TDO_0), ZB1.808 (2_3)
/BeagleBone/TMS: U1.M7 (TMS_0), ZB1.810 (2_4)
EWP: R305.2, U301.7 (WP); also elsewhere on the board
G022: ZB1.819 (0_22); also elsewhere on the board
G023: ZB1.813 (0_23); also elsewhere on the board
G026: ZB1.814 (0_26); also elsewhere on the board
G027: ZB1.817 (0_27); also elsewhere on the board
G112: ZB1.812 (1_12); also elsewhere on the board
G113: ZB1.811 (1_13); also elsewhere on the board
G114: ZB1.816 (1_14); also elsewhere on the board
G115: ZB1.815 (1_15); also elsewhere on the board
G129: ZB1.826 (1_29); also elsewhere on the board
G201: ZB1.818 (2_1); also elsewhere on the board
SCLK: U1.E8 (CCLK_0), ZB1.922 (0_2_spi0_sclk); also elsewhere on the board

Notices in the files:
sub1/sub2/sub3 kicad/KiwiSDR/kiwi.kicad_pcb:
© John Seamons
sub1/sub2/sub3 kicad/active_antenna/ant.kicad_pcb:
© John Seamons, ZL/KF6VO
© Sonoran Radio Research
